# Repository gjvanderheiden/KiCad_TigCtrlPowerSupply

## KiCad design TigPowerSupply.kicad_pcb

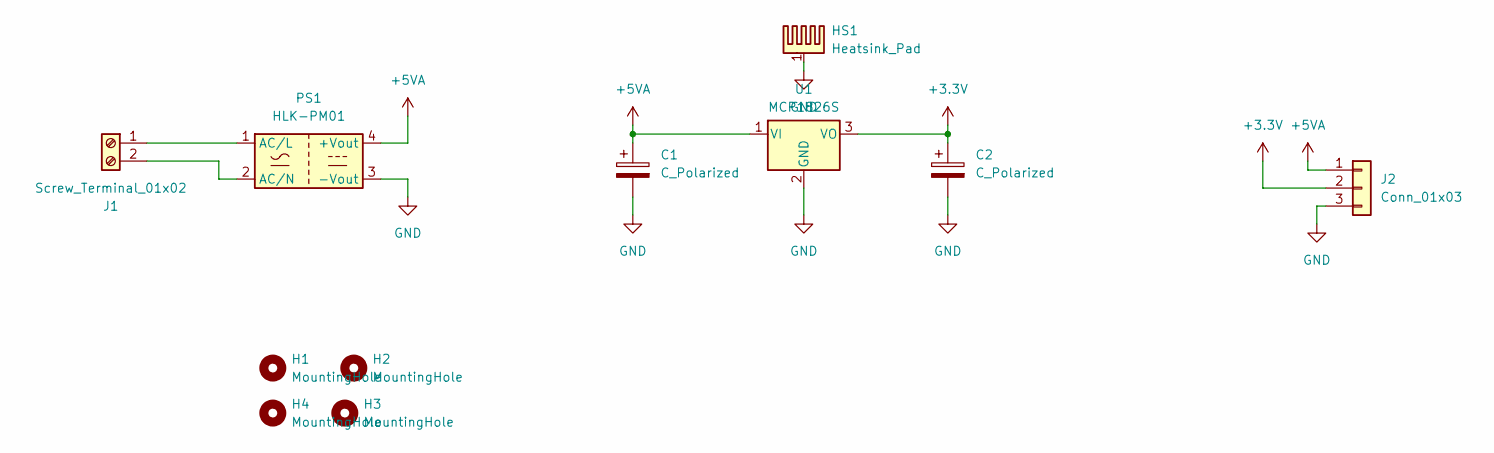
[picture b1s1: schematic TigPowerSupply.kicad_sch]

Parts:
C1, C2: C_Polarized; CP_Radial_D4.0mm_P1.50mm
H1, H2, H3, H4: MountingHole; MountingHole_3.2mm_M3_DIN965
HS1: Heatsink_Pad; Heatsink_10x15x40_TTO220
J1: Screw_Terminal_01x02; TerminalBlock_Phoenix_MKDS-1,5-2-5.08_1x02_P5.08mm_Horizont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
J2: Conn_01x03; JST_PH_B3B-PH-K_1x03_P2.00mm_Vertical
PS1: HLK-PM01; Converter_ACDC_Hi-Link_HLK-PMxx
U1: MCP1826S; TO-220-3_Vertical

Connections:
+3.3V: C2.1, J2.2, U1.3 (VO)
+5VA: C1.1, J2.1, PS1.4 (+Vout), U1.1 (VI)
GND: C1.2, C2.2, HS1.1, J2.3, PS1.3 (-Vout), U1.2 (GND)
unnamed: J1.1, PS1.1 (AC/L)
unnamed: J1.2, PS1.2 (AC/N)

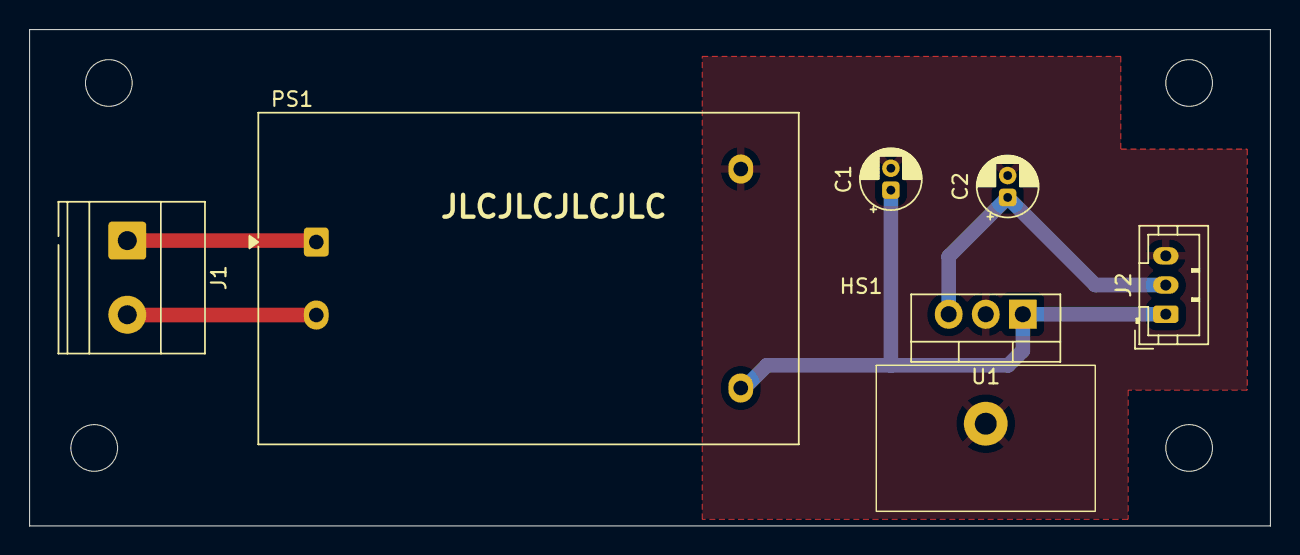
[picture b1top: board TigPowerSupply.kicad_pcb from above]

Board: 2 copper layers, 85.0 x 34.0 mm, 11 parts (0 on the bottom side), 5 nets.

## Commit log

2025-02-01 init
2025-02-06 tweaked the dimensions to be round mm values
2025-08-31 moved regulator and changed output connector
